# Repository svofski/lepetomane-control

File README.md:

# Pétocontrôle

This is a MIDI control surface that sends CC messages when you turn the knobs. The main features are:

 * magnetic encoders (AS5600) with real potentiometer mechanics for ultra-smooth potentiometer-like feel
 * beautiful 0402 orange LEDs that show knob positions
 * Futaba 8-MD-06INKM VFD display

I wanted smooth feel encoders that work like proper potentiometers. These days everything is implemented using notchy encoders and although smooth input encoders do exist, they are somewhat uncommon.

The design consists of two boards, the bottom one has MCU and the sensors, the top "mezzanine" board has the shift registers for the LEDs and holes for the knob shafts. 
The knobs are mechanisms ripped out from cheap potentiometers, they have little magnets glued into their bottom ends. Several boards can in theory attach to one another to form long strips of knobs.

## Design files
 * [Schematics and PCB (KiCanvas)](https://kicanvas.org/?github=https://github.com/svofski/lepetomane-control/tree/master/kicad)

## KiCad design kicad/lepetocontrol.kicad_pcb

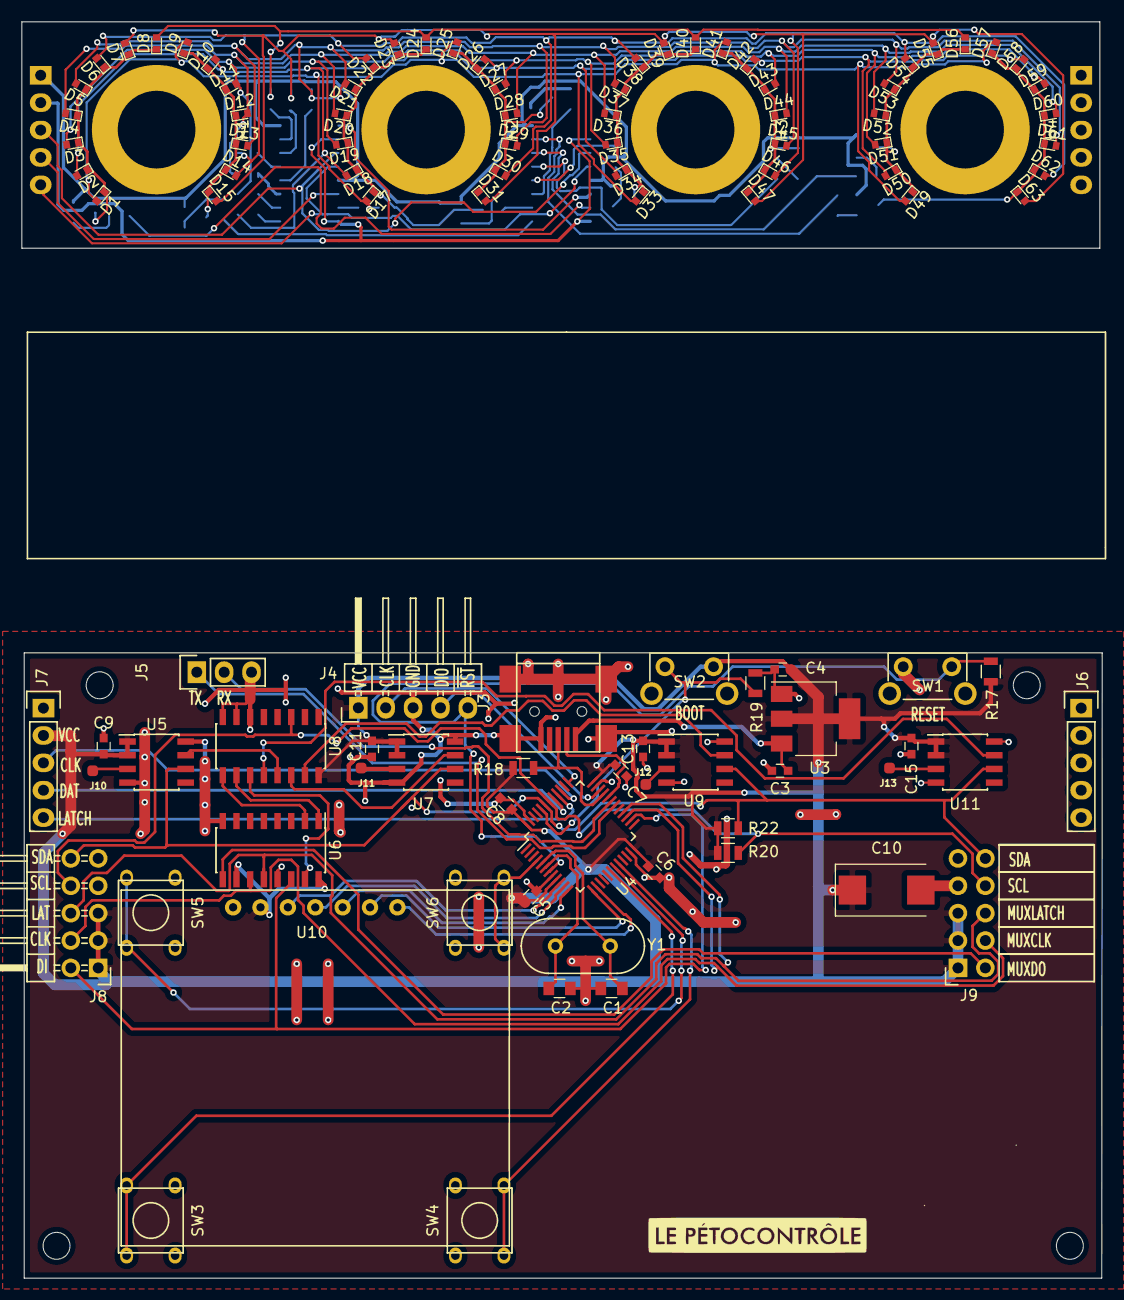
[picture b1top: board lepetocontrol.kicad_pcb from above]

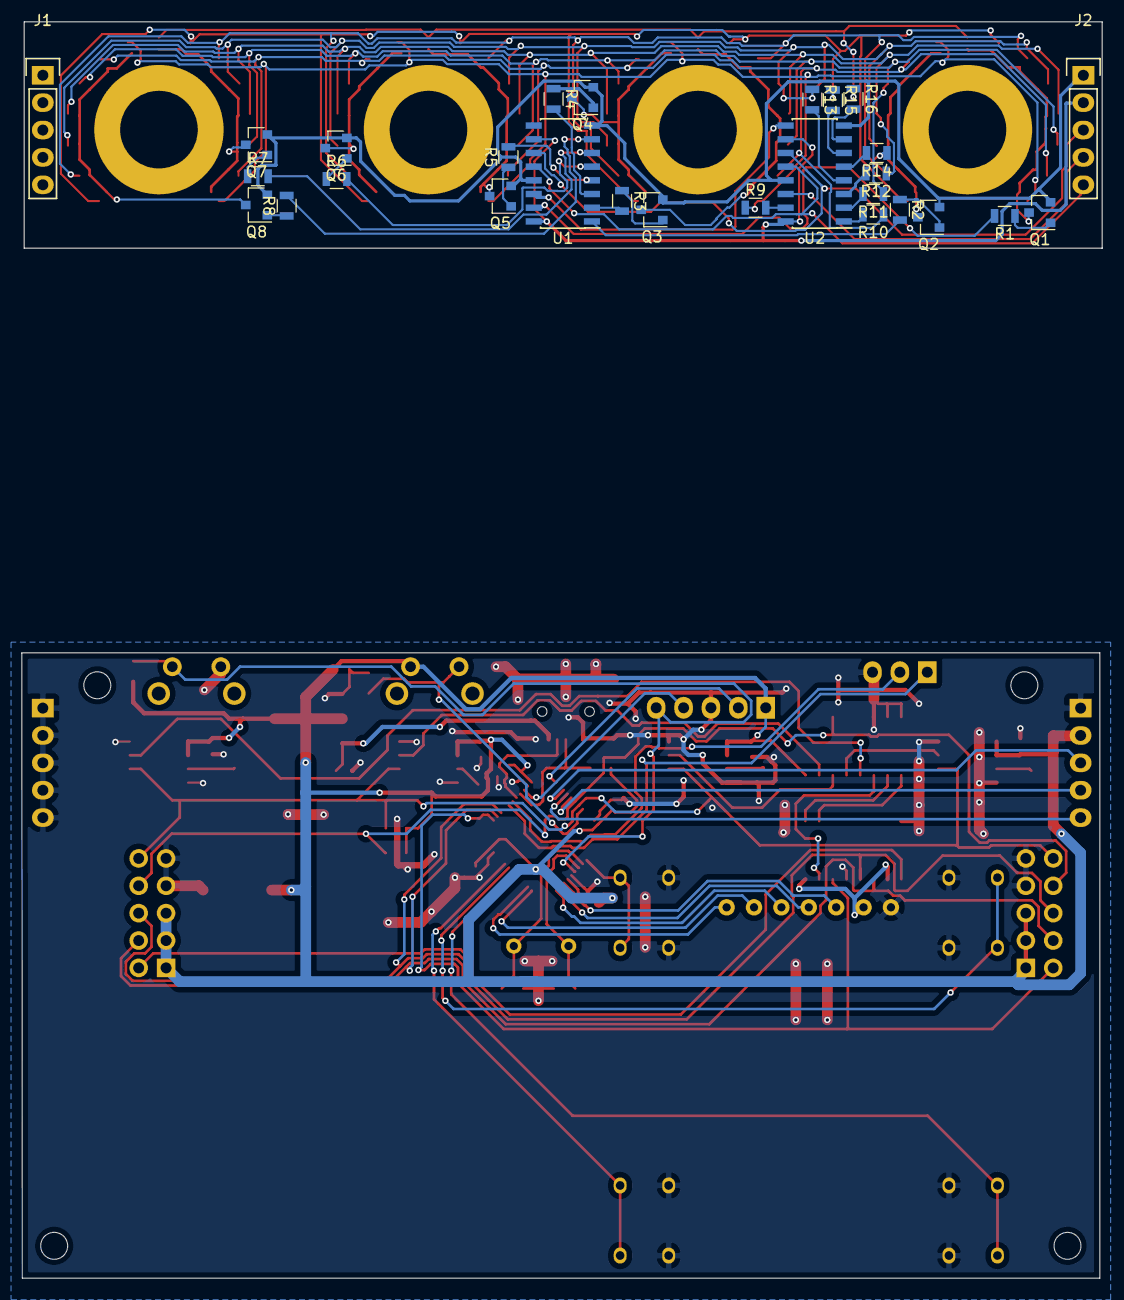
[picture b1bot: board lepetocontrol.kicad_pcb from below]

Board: 2 copper layers, 100.2 x 116.5 mm, 142 parts (28 on the bottom side), 86 nets.

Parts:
C1, C2: 20p; C_0805
C3, C4, C5, C6, C7, C8, C9, C11, C13, C15: 100nF; C_0603
C10: 220uF; CP_Tantalum_Case-D_EIA-7343-31_Reflow
D1, D2, D3, D4, D5, D6, D7, D8, D9, D10, D11, D12, D13, D14, D15, D17, D18, D19, D20, D21, D22, D23, D24, D25, D26, D27, D28, D29, D30, D31, D33, D34, D35, D36, D37, D38, D39, D40, D41, D42, D43, D44, D45, D46, D47, D49, D50, D51, D52, D53, D54, D55, D56, D57, D58, D59, D60, D61, D62, D63: LED; LED_0402
H1, H2, H3, H4: MountingHole; pot-mounting-hole
H5, H6, H7, H8: MountingHole; MountingHole_2.5mm
J1, J2: 1x05; Pin_Header_Straight_1x05
J3: USB_OTG; USB_Mini-B
J4: Conn_01x05; Pin_Header_Angled_1x05
J5: Conn_01x03; Pin_Header_Straight_1x03
J6, J7: Conn_01x05_Female; Socket_Strip_Straight_1x05
J8: Conn_02x05_Odd_Even; Pin_Header_Angled_2x05
J9: Conn_02x05_Odd_Even; Socket_Strip_Angled_2x05
J10: SENSE1; WIREPAD_SMD_TINY
J11: SENSE2; WIREPAD_SMD_TINY
J12: SENSE3; WIREPAD_SMD_TINY
J13: SENSE4; WIREPAD_SMD_TINY
MEZZANINE: lepetocontrol-mezzanine
Q1, Q2, Q3, Q4, Q5, Q6, Q7, Q8: BC817; SOT-23
R1, R2, R3, R4, R5, R6, R7, R8: 1K; R_0805
R9, R10, R11, R12, R13, R14, R15, R16: 100; R_0805
R17, R19: 10K; R_0805
R18: 1K5; R_0805
R20, R22: 2K7; R_0805
SW1, SW2: SW; SW_Tactile_SPST_Angled
SW3, SW4, SW5, SW6: SW; switch_6x6
U1, U2, U6: 74HC595; SOIC-16_3.9x9.9mm_Pitch1.27mm
U3: LM1117-3.3; SOT-223-3Lead_TabPin2
U4: STM32F103C4Tx; LQFP-48_7x7mm_Pitch0.5mm
U5, U7, U9, U11: AS5600; SOIC-8_3.9x4.9mm_Pitch1.27mm
U8: 74HC4051; SOIC-16_3.9x9.9mm_Pitch1.27mm
U10: oled-7pin; oled_1.3_spi
Y1: 8MHz; HC-49V

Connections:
/CLK: J2.3, U1.11, U2.11
/DATA: J2.4, U2.14
/LATCH: J2.5, U1.12, U2.12
/mcu/BUTT1: SW6.2, U4.4
/mcu/BUTT2: SW3.2, U4.18
/mcu/BUTT3: SW5.2, U4.19
/mcu/BUTT4: SW4.2, U4.20
/mcu/LED_CLK: J7.3, U4.39
/mcu/LED_DATA: J7.4, U4.41
/mcu/LED_LATCH: J7.5, U4.40
/mcu/MUXCLK: J8.4, J9.4, U4.27, U6.11
/mcu/MUXDI: J8.2, U4.26, U6.14
/mcu/MUXDO: J9.2, U6.9
/mcu/MUXLATCH: J8.6, J9.6, U4.28, U6.12
/mcu/OLED_CS: U4.14, U10.7
/mcu/OLED_DC: U4.13, U10.6
/mcu/OLED_SCK: U4.10, U10.3
/mcu/OLED_SDA: U4.11, U10.4
/mcu/RXD: J5.2, U4.31
/mcu/SCL: J8.8, J9.8, R20.1, U4.42, U8.3
/mcu/SCL1: U5.7, U8.13
/mcu/SCL2: U7.7, U8.14
/mcu/SCL3: U8.15, U9.7
/mcu/SCL4: U8.12, U11.7
/mcu/SDA: J8.10, J9.10, R22.2, U4.43, U5.6, U7.6, U9.6, U11.6
/mcu/SENSE1: J10.1, U5.3
/mcu/SENSE2: J11.1, U7.3
/mcu/SENSE3: J12.1, U9.3
/mcu/SENSE4: J13.1, U11.3
/mcu/SWCLK: J4.2, U4.37
/mcu/SWDIO: J4.4, U4.34
/mcu/TXD: J5.1, U4.30
/mcu/USB_DM: J3.2, U4.32
/mcu/USB_DP: J3.3, R18.2, U4.33
/mcu/VBUS: C3.2, J3.1, U3.3
/mcu/~OLED_RES: U4.12, U10.5
/mcu/~RESET: J4.5, R17.2, SW1.2, U4.7
GND: C1.1, C2.2, C3.1, C4.2, C5.2, C6.2, C7.2, C8.2, C9.2, C10.2, C11.2, C13.2, C15.2, J2.1, J3.5, J3.6, J4.3, J5.3, J6.1, J6.2, J6.3, J6.4, J6.5, J7.1, J8.7, J8.9, J9.7, J9.9, Q1.2, Q2.2, Q3.2, Q4.2, Q5.2, Q6.2, Q7.2, Q8.2, R19.2, SW1.1, SW3.1, SW4.1, SW5.1, SW6.1, U1.8, U1.13, U2.8, U2.13, U3.1, U4.8, U4.23, U4.35, U4.47, U5.4, U5.8, U6.8, U6.13, U7.4, U7.8, U8.6, U8.7, U8.8, U9.4, U9.8, U10.1, U11.4, U11.8
unnamed: C1.2, U4.5, Y1.1
unnamed: C2.1, U4.6, Y1.2
unnamed: D1.1, D2.1, D3.1, D4.1, D5.1, D6.1, D7.1, D8.1, Q1.3
unnamed: D1.2, D9.2, D17.2, D25.2, D33.2, D41.2, D49.2, D57.2, R9.1
unnamed: D9.1, D10.1, D11.1, D12.1, D13.1, D14.1, D15.1, Q2.3
unnamed: D2.2, D10.2, D18.2, D26.2, D34.2, D42.2, D50.2, D58.2, R10.1
unnamed: D3.2, D11.2, D19.2, D27.2, D35.2, D43.2, D51.2, D59.2, R11.1
unnamed: D4.2, D12.2, D20.2, D28.2, D36.2, D44.2, D52.2, D60.2, R12.1
unnamed: D5.2, D13.2, D21.2, D29.2, D37.2, D45.2, D53.2, D61.2, R13.1
unnamed: D6.2, D14.2, D22.2, D30.2, D38.2, D46.2, D54.2, D62.2, R14.1
unnamed: D7.2, D15.2, D23.2, D31.2, D39.2, D47.2, D55.2, D63.2, R15.1
unnamed: D17.1, D18.1, D19.1, D20.1, D21.1, D22.1, D23.1, D24.1, Q3.3
unnamed: D8.2, D24.2, D40.2, D56.2, R16.1
unnamed: D25.1, D26.1, D27.1, D28.1, D29.1, D30.1, D31.1, Q4.3
unnamed: D33.1, D34.1, D35.1, D36.1, D37.1, D38.1, D39.1, D40.1, Q5.3
unnamed: D41.1, D42.1, D43.1, D44.1, D45.1, D46.1, D47.1, Q6.3
unnamed: D49.1, D50.1, D51.1, D52.1, D53.1, D54.1, D55.1, D56.1, Q7.3
unnamed: D57.1, D58.1, D59.1, D60.1, D61.1, D62.1, D63.1, Q8.3
unnamed: Q1.1, R1.1
unnamed: Q2.1, R2.1
unnamed: Q3.1, R3.1
unnamed: Q4.1, R4.1
unnamed: Q5.1, R5.1
unnamed: Q6.1, R6.1
unnamed: Q7.1, R7.1
unnamed: Q8.1, R8.1
unnamed: R1.2, U1.15
unnamed: R2.2, U1.1
unnamed: R3.2, U1.2
unnamed: R4.2, U1.3
unnamed: R5.2, U1.4
unnamed: R6.2, U1.5
unnamed: R7.2, U1.6
unnamed: R8.2, U1.7
unnamed: R9.2, U2.15
unnamed: R10.2, U2.1
unnamed: R11.2, U2.2
unnamed: R12.2, U2.3
unnamed: R13.2, U2.4
unnamed: R14.2, U2.5
unnamed: R15.2, U2.6
unnamed: R16.2, U2.7
unnamed: R19.1, SW2.1, U4.44
unnamed: U1.14, U2.9
unnamed: U6.1, U8.10
unnamed: U6.2, U8.9
unnamed: U6.15, U8.11
VCC: C4.1, C5.1, C6.1, C7.1, C8.1, C9.1, C10.1, C11.1, C13.1, C15.1, J2.2, J4.1, J7.2, J8.1, J8.3, J8.5, J9.1, J9.3, J9.5, R17.1, R18.1, R20.2, R22.1, SW2.2, U1.10, U1.16, U2.10, U2.16, U3.2, U4.9, U4.24, U4.36, U4.48, U5.1, U5.2, U6.10, U6.16, U7.1, U7.2, U8.16, U9.1, U9.2, U10.2, U11.1, U11.2

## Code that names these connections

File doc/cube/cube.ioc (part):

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Mcu.Name=STM32F103C(4-6)Tx
Mcu.Package=LQFP48
Mcu.UserName=STM32F103C6Tx
PA0-WKUP.GPIOParameters=GPIO_Label
PA0-WKUP.GPIO_Label=OLED_SCK
PA0-WKUP.Signal=GPIO_Output
PA1.GPIOParameters=GPIO_Label
PA1.GPIO_Label=OLED_SDA
PA1.Signal=GPIO_Output
PA10.Mode=Asynchronous
PA10.Signal=USART1_RX
PA11.Mode=Device
PA11.Signal=USB_DM
PA12.Mode=Device
PA12.Signal=USB_DP
PA13.Mode=Serial_Wire
PA13.Signal=SYS_JTMS-SWDIO
PA14.Mode=Serial_Wire
PA14.Signal=SYS_JTCK-SWCLK
PA15.GPIOParameters=GPIO_Label,GPIO_ModeDefaultOutputPP
PA15.GPIO_Label=SDA
PA15.GPIO_ModeDefaultOutputPP=GPIO_MODE_OUTPUT_OD
PA15.Signal=GPIO_Output
PA2.GPIOParameters=GPIO_Label
PA2.GPIO_Label=OLED_RES
PA2.Signal=GPIO_Output
PA3.GPIOParameters=GPIO_Label
PA3.GPIO_Label=OLED_DC
PA3.Signal=GPIO_Output
PA4.GPIOParameters=GPIO_Label
PA4.GPIO_Label=OLED_CS
PA4.Signal=GPIO_Output
PA9.Mode=Asynchronous
PA9.Signal=USART1_TX
PB0.GPIOParameters=GPIO_PuPd,GPIO_Label
PB0.GPIO_Label=BUTT2
PB0.GPIO_PuPd=GPIO_PULLUP
PB0.Signal=GPIO_Input
PB1.GPIOParameters=GPIO_PuPd,GPIO_Label
PB1.GPIO_Label=BUTT3
PB1.GPIO_PuPd=GPIO_PULLUP
PB1.Signal=GPIO_Input
PB10.GPIOParameters=GPIO_Label
PB10.GPIO_Label=SCL3
PB10.Signal=GPIO_Input
PB11.GPIOParameters=GPIO_Label
PB11.GPIO_Label=SCL4
PB11.Signal=GPIO_Input
PB12.GPIOParameters=GPIO_Label
PB12.GPIO_Label=SCL5
PB12.Signal=GPIO_Input
PB13.GPIOParameters=GPIO_Label
PB13.GPIO_Label=SCL6
PB13.Signal=GPIO_Input
PB14.GPIOParameters=GPIO_Label
PB14.GPIO_Label=SCL7
PB14.Signal=GPIO_Input
PB15.GPIOParameters=GPIO_Label
PB15.GPIO_Label=SCL8
PB15.Signal=GPIO_Input
PB2.GPIOParameters=GPIO_PuPd,GPIO_Label
PB2.GPIO_Label=BUTT3
PB2.GPIO_PuPd=GPIO_PULLUP
PB2.Signal=GPIO_Input
PB3.Mode=TX_Only_Simplex_Unidirect_Master
PB3.Signal=SPI1_SCK
PB4.GPIOParameters=GPIO_Label
PB4.GPIO_Label=LED_LATCH
PB4.Signal=GPIO_Output
PB5.Mode=TX_Only_Simplex_Unidirect_Master
PB5.Signal=SPI1_MOSI
PB6.Mode=I2C
PB6.Signal=I2C1_SCL
PB7.Mode=I2C
PB7.Signal=I2C1_SDA
PB8.GPIOParameters=GPIO_Label
PB8.GPIO_Label=SCL1
PB8.Signal=GPIO_Input
PB9.GPIOParameters=GPIO_Label
PB9.GPIO_Label=SCL2
PB9.Signal=GPIO_Input
PC13-TAMPER-RTC.GPIOParameters=GPIO_Label
PC13-TAMPER-RTC.GPIO_Label=OLED_RST
PC13-TAMPER-RTC.Signal=GPIO_Output
PC15-OSC32_OUT.GPIOParameters=GPIO_PuPd,GPIO_Label
PC15-OSC32_OUT.GPIO_Label=BUTT1
PC15-OSC32_OUT.GPIO_PuPd=GPIO_PULLUP
PC15-OSC32_OUT.Signal=GPIO_Input
PD0-OSC_IN.Mode=HSE-External-Oscillator
PD0-OSC_IN.Signal=RCC_OSC_IN
PD1-OSC_OUT.Mode=HSE-External-Oscillator
PD1-OSC_OUT.Signal=RCC_OSC_OUT
RCC.SYSCLKFreq_VALUE=48000000
RCC.SYSCLKSource=RCC_SYSCLKSOURCE_PLLCLK
board=custom

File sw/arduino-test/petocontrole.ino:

#include <USBComposite.h>
#include <SPI.h>

//#include <SoftWire.h>
//extern SoftWire Wire;
#include <Wire.h>

#include "AS5600.h"

#define WITH_LEDS 1
#define LED_LATCH PB4

#define MUXDI     PB13
#define MUXCLK    PB14
#define MUXLATCH  PB15

#define STROBE_US 1

#define PWM_BITS 7

//1/(1+EXP(((A2/21)-6)*-1))*255
const uint8_t pwm_linearize[128] = 
{
                                                    
    0x01, 0x01, 0x01, 0x01, 0x01, 0x01, 0x01, 0x01, 
    0x01, 0x01, 0x01, 0x01, 0x01, 0x02, 0x02, 0x02, 
    0x02, 0x03, 0x03, 0x03, 0x04, 0x04, 0x04, 0x05, 
    0x05, 0x06, 0x07, 0x07, 0x08, 0x09, 0x0A, 0x0B, 
    0x0C, 0x0D, 0x0E, 0x0F, 0x11, 0x12, 0x14, 0x16, 
    0x18, 0x1A, 0x1C, 0x1F, 0x21, 0x24, 0x27, 0x2B, 
    0x2E, 0x32, 0x36, 0x3A, 0x3E, 0x43, 0x47, 0x4C, 
    0x51, 0x57, 0x5C, 0x62, 0x67, 0x6D, 0x73, 0x79, 
    0x7F, 0x85, 0x8B, 0x91, 0x97, 0x9C, 0xA2, 0xA7, 
    0xAD, 0xB2, 0xB7, 0xBB, 0xC0, 0xC4, 0xC8, 0xCC, 
    0xD0, 0xD3, 0xD7, 0xDA, 0xDD, 0xDF, 0xE2, 0xE4, 
    0xE6, 0xE8, 0xEA, 0xEC, 0xED, 0xEF, 0xF0, 0xF1, 
    0xF2, 0xF3, 0xF4, 0xF5, 0xF6, 0xF7, 0xF7, 0xF8, 
    0xF9, 0xF9, 0xFA, 0xFA, 0xFA, 0xFB, 0xFB, 0xFB, 
    0xFC, 0xFC, 0xFC, 0xFC, 0xFD, 0xFD, 0xFD, 0xFD, 
    0xFD, 0xFD, 0xFD, 0xFD, 0xFE, 0xFE, 0xFE, 0xFF, 
};

USBCompositeSerial CompositeSerial;


#define STROBE(pin) {digitalWrite(pin, 1); delay_us(STROBE_US); digitalWrite(pin, 0); /*delay_us(STROBE_US);*/}

class myMidi : public USBMIDI {
    virtual void handleNoteOff(unsigned int channel, unsigned int note, unsigned int velocity) {
        //noTone(SPEAKER_PIN);
    }
    virtual void handleNoteOn(unsigned int channel, unsigned int note, unsigned int velocity) {
        //tone(SPEAKER_PIN, (midiNoteFrequency_10ths[note]+5)/10);
        CompositeSerial.print("midi note on chan="); CompositeSerial.println(note);
    }

};

myMidi midi;
AMS_5600 as5600;

void iicmux_init()
{
    pinMode(MUXDI, OUTPUT);
    pinMode(MUXCLK, OUTPUT);
    pinMode(MUXLATCH, OUTPUT);
    digitalWrite(MUXDI, 0);
    digitalWrite(MUXCLK, 0);
    digitalWrite(MUXLATCH, 0);
}

// on one board there are 4 devices 0..3
void iicmux_sel(int dev)
{  
    uint8_t value = dev;
    for (int i = 0; i < 8; ++i) {
        digitalWrite(MUXDI, 1 & (value >> 7));
        STROBE(MUXCLK);
        value <<= 1;
    }
    STROBE(MUXLATCH);
}

int poll_knob(int n)
{
    iicmux_sel(n);

    rcc_clk_enable(RCC_I2C1);
    int result = as5600.getScaledAngle();
    rcc_clk_disable(RCC_I2C1);

    return result;
}

void begin_spi()
{
    afio_remap(AFIO_REMAP_SPI1);
    // setup SPI1 for LED shift registers
    SPI.begin();
    SPI.setBitOrder(MSBFIRST);
    SPI.setDataMode(SPI_MODE2);    
    SPI.setClockDivider(SPI_CLOCK_DIV4);      // Slow speed (72 / 16 = 4.5 MHz SPI_1 speed)
    pinMode(LED_LATCH, OUTPUT); // SPI MISO is actually SR latch
}

#if 0
void end_spi()
{
    SPI.end();
    afio_unremap(AFIO_REMAP_SPI1);
    SPI.begin();
    SPI.end();
    rcc_clk_disable(RCC_SPI1);
}
#endif

void setup() {
    // this makes boot/reset buttons necessary for uploading via st-link
    disableDebugPorts();
    //enableDebugPorts();

    USBComposite.setProductId(0x0030);
    midi.registerComponent();
    CompositeSerial.registerComponent();
    USBComposite.begin();

    // i2c 
    Wire.begin();
    rcc_clk_disable(RCC_I2C1);
    iicmux_init();
    iicmux_sel(0);


#if WITH_LEDS
    begin_spi();
#endif
    pinMode(LED_LATCH, OUTPUT); // SPI MISO is actually SR latch
}



long lastmillis = millis();
int delaytime = 0;

#define N_KNOBS 4
#define N_LED_GROUPS (N_KNOBS * 2)
// 15 leds per knob

struct LedRefresh {
    union {
        uint8_t bitmap[N_LED_GROUPS];
        uint16_t bitmap16[N_KNOBS];
    };
    int index;

    LedRefresh() : bitmap{}, index(0) {}

    void refresh()
    {
        digitalWrite(LED_LATCH, 0);
        SPI.transfer16(0);
        digitalWrite(LED_LATCH, 1);
        digitalWrite(LED_LATCH, 0);    

        digitalWrite(LED_LATCH, 0);
        SPI.transfer16((1 << (index + 8)) | bitmap[index]);
        digitalWrite(LED_LATCH, 1);
        digitalWrite(LED_LATCH, 0);    
        //STROBE(LED_LATCH);


        ++index;
        if (index == N_LED_GROUPS) {
            index = 0;
        }    
    }

    void off()
    {
        SPI.transfer(0);
        SPI.transfer(0);
        STROBE(LED_LATCH);  
    }
};

struct Knob {
    static constexpr int deadzone = 4096 - 4096 * 5 / 6;
    static constexpr int half_deadzone = deadzone / 2;
    int min_value = 0;
    int max_value = 4095 - deadzone;
    int raw_value; // 0..4095
    int deadzoned_value;
    int id;

    Knob(int id) : id(id) {}

    int poll() {
        iicmux_sel(id);

        rcc_clk_enable(RCC_I2C1);
        raw_value = as5600.getScaledAngle();
        rcc_clk_disable(RCC_I2C1);


        deadzoned_value = raw_value - half_deadzone;
        if (deadzoned_value < 0) deadzoned_value = 0;
        if (deadzoned_value > max_value) deadzoned_value = max_value;
        deadzoned_value = deadzoned_value * 1200 / 1000;

        return raw_value;
    }

    int16_t get_bitmap(int pwm_phase)
    {
#if 1
        constexpr int mult = 1 << PWM_BITS;
        int nbits = 1 + deadzoned_value * 15 * mult / 4096;
        uint8_t frac = nbits & (mult - 1);

        frac = pwm_linearize[frac]>>1;

        int num = nbits >> PWM_BITS;
        if (frac >= pwm_phase) ++num;
        int bm = (1 << num) - 1;
        return bm;
#else
        int nbits = 1 + deadzoned_value * 15 / 4096;
        return 1 << nbits;
#endif
    }
};

LedRefresh leds;
Knob knobs[N_KNOBS] {Knob(0), Knob(1), Knob(2), Knob(3)};

int slowctr = 0;

#define KNOB_POLL 512
int knob_poll_ctr = 0;
int rr_knob = 0;
int rr_pwm = 0;
int pwm_phase = 0;

void loop() {
    midi.poll();

    leds.refresh();
    //delay_us(10);

    if (++rr_pwm == N_KNOBS*2) {
        rr_pwm = 0;
        if (++pwm_phase == (1 << PWM_BITS)) {
            pwm_phase = 0;
        }
        for (int i = 0; i < N_KNOBS; ++i) {
            leds.bitmap16[i] = knobs[i].get_bitmap(pwm_phase);
        }
    }

    if (++knob_poll_ctr == KNOB_POLL) {
        knob_poll_ctr = 0;

        leds.off();
        knobs[rr_knob].poll();
        if (++rr_knob == N_KNOBS) rr_knob = 0;
    }
}

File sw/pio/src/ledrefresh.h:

// LED refresher for petocontrole
//
// The LEDs are arranged in a 8x8 matrix (row 7 of odd columns is absent).
// Consult the schematics for details.
//
// svofski 2024

#pragma once

#include "params.h"

#include <cstdint>
#include <libopencm3/stm32/gpio.h>
#include <libopencm3/stm32/spi.h>

void spi_reset(int dev)
{
    switch (dev) {
        case SPI1:
            rcc_periph_reset_pulse(RST_SPI1);
            break;
        case SPI2:
            rcc_periph_reset_pulse(RST_SPI2);
            break;
        default:
            for(;;);
    }
}


// LED_CLK      PB3     SPI1_SCK (remapped)
// LED_LATCH    PB4     (GPIO)
// LED_DATA     PB5     SPI1_MOSI (remapped)
//template<int N_KNOBS, int N_LED_GROUPS>
struct LedRefresh {
    static constexpr uint32_t gpio_port = GPIOB;
    static constexpr uint32_t gpio_clk = GPIO3,
                       gpio_latch = GPIO4,
                       gpio_data = GPIO5; 

    union {
        uint8_t bitmap[N_LED_GROUPS]; // LED matrix columns
        uint16_t bitmap16[N_KNOBS];   // each knob has 15 leds (2 columns)
    };

    int index;

    LedRefresh() : bitmap{}, index(0) {}

    void init()
    {
        /* Enable Alternate Function clock. */
	rcc_periph_clock_enable(RCC_AFIO);
        /* Enable SPI1 clock */
        rcc_periph_clock_enable(RCC_SPI1);

        /* remap SPI1 to PB3..5 */
        gpio_primary_remap(AFIO_MAPR_SWJ_CFG_JTAG_OFF_SW_ON, AFIO_MAPR_SPI1_REMAP);
        
        gpio_set_mode(gpio_port, GPIO_MODE_OUTPUT_50_MHZ,
            GPIO_CNF_OUTPUT_ALTFN_PUSHPULL, gpio_clk | gpio_data | gpio_latch );

        spi_reset(SPI1);

        spi_init_master(SPI1, 
                SPI_CR1_BAUDRATE_FPCLK_DIV_16, 
                SPI_CR1_CPOL_CLK_TO_0_WHEN_IDLE,
                SPI_CR1_CPHA_CLK_TRANSITION_2,
                SPI_CR1_DFF_16BIT,
                SPI_CR1_MSBFIRST);

        spi_set_bidirectional_transmit_only_mode(SPI1);

        // examples have this but i don't know why...
        spi_enable_software_slave_management(SPI1);
        spi_set_nss_high(SPI1);

        spi_enable(SPI1);

        gpio_set_mode(gpio_port, GPIO_MODE_OUTPUT_50_MHZ,
                GPIO_CNF_OUTPUT_PUSHPULL, gpio_latch);
    }

    void latch(int on)
    {
        if (on) {
            gpio_set(gpio_port, gpio_latch);
            for (unsigned i = 0; i < 5; ++i) { __asm__("nop"); }
        }
        else {
            gpio_clear(gpio_port, gpio_latch);
            for (unsigned i = 0; i < 35; ++i) { __asm__("nop"); }
        }
    }

    void strobe()
    {
        latch(0);
        latch(1);
        latch(0);
    }

    // iterate with 1 as column selector (group) in msb and bitmap as rows in lsb
    void refresh()
    {
        spi_send(SPI1, 0);
        latch(1);
        latch(0);

        spi_send(SPI1, (1 << (index + 8)) | bitmap[index]);
        latch(1);
        latch(0);

        ++index;
        if (index == N_LED_GROUPS) {
            index = 0;
        }
    }

    void off()
    {
        spi_send(SPI1, 0);
        strobe();
    }
};

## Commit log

2024-11-16 first commit from salvaged pieces
    everything needs a lot of cleanup before this can continue. but it
    builds, the leds shine beautifully and it sends midi cc messages.
2024-11-16 pics
2024-11-23 peak display for midi mixer, some improvements
2024-11-25 wip wip wip
    kicad files updated to version 8
    vfd added
2024-11-25 moving code around
